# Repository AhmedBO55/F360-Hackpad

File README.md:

# F360-Hackpad
So, as a user of CAD software such as Fusion 360 and SolidWorks, most of the time I only use a small range of shortcuts, so there is basically no need for a full-size keyboard, and a macro pad is enough for the job. So, I will use 16 MX switches and a 128×32 OLED screen in order to determine the layer of the macropad. With that, I will not use a keyboard: I will use the first layer for shortcuts and the second layer for using numbers, so I will not need a keyboard.

---

# Schematics :

---

# PCB :

---

# CAD : 

---
# BOM :

1 SEED XIAO RP2040 (through-hole version)

1 0.91 inch 128*32 OLED Display

16 MX switches

16 DSA Keycaps

16 1N4148 Diodes

5 M3-16 screws

5 M3 heatset inserts

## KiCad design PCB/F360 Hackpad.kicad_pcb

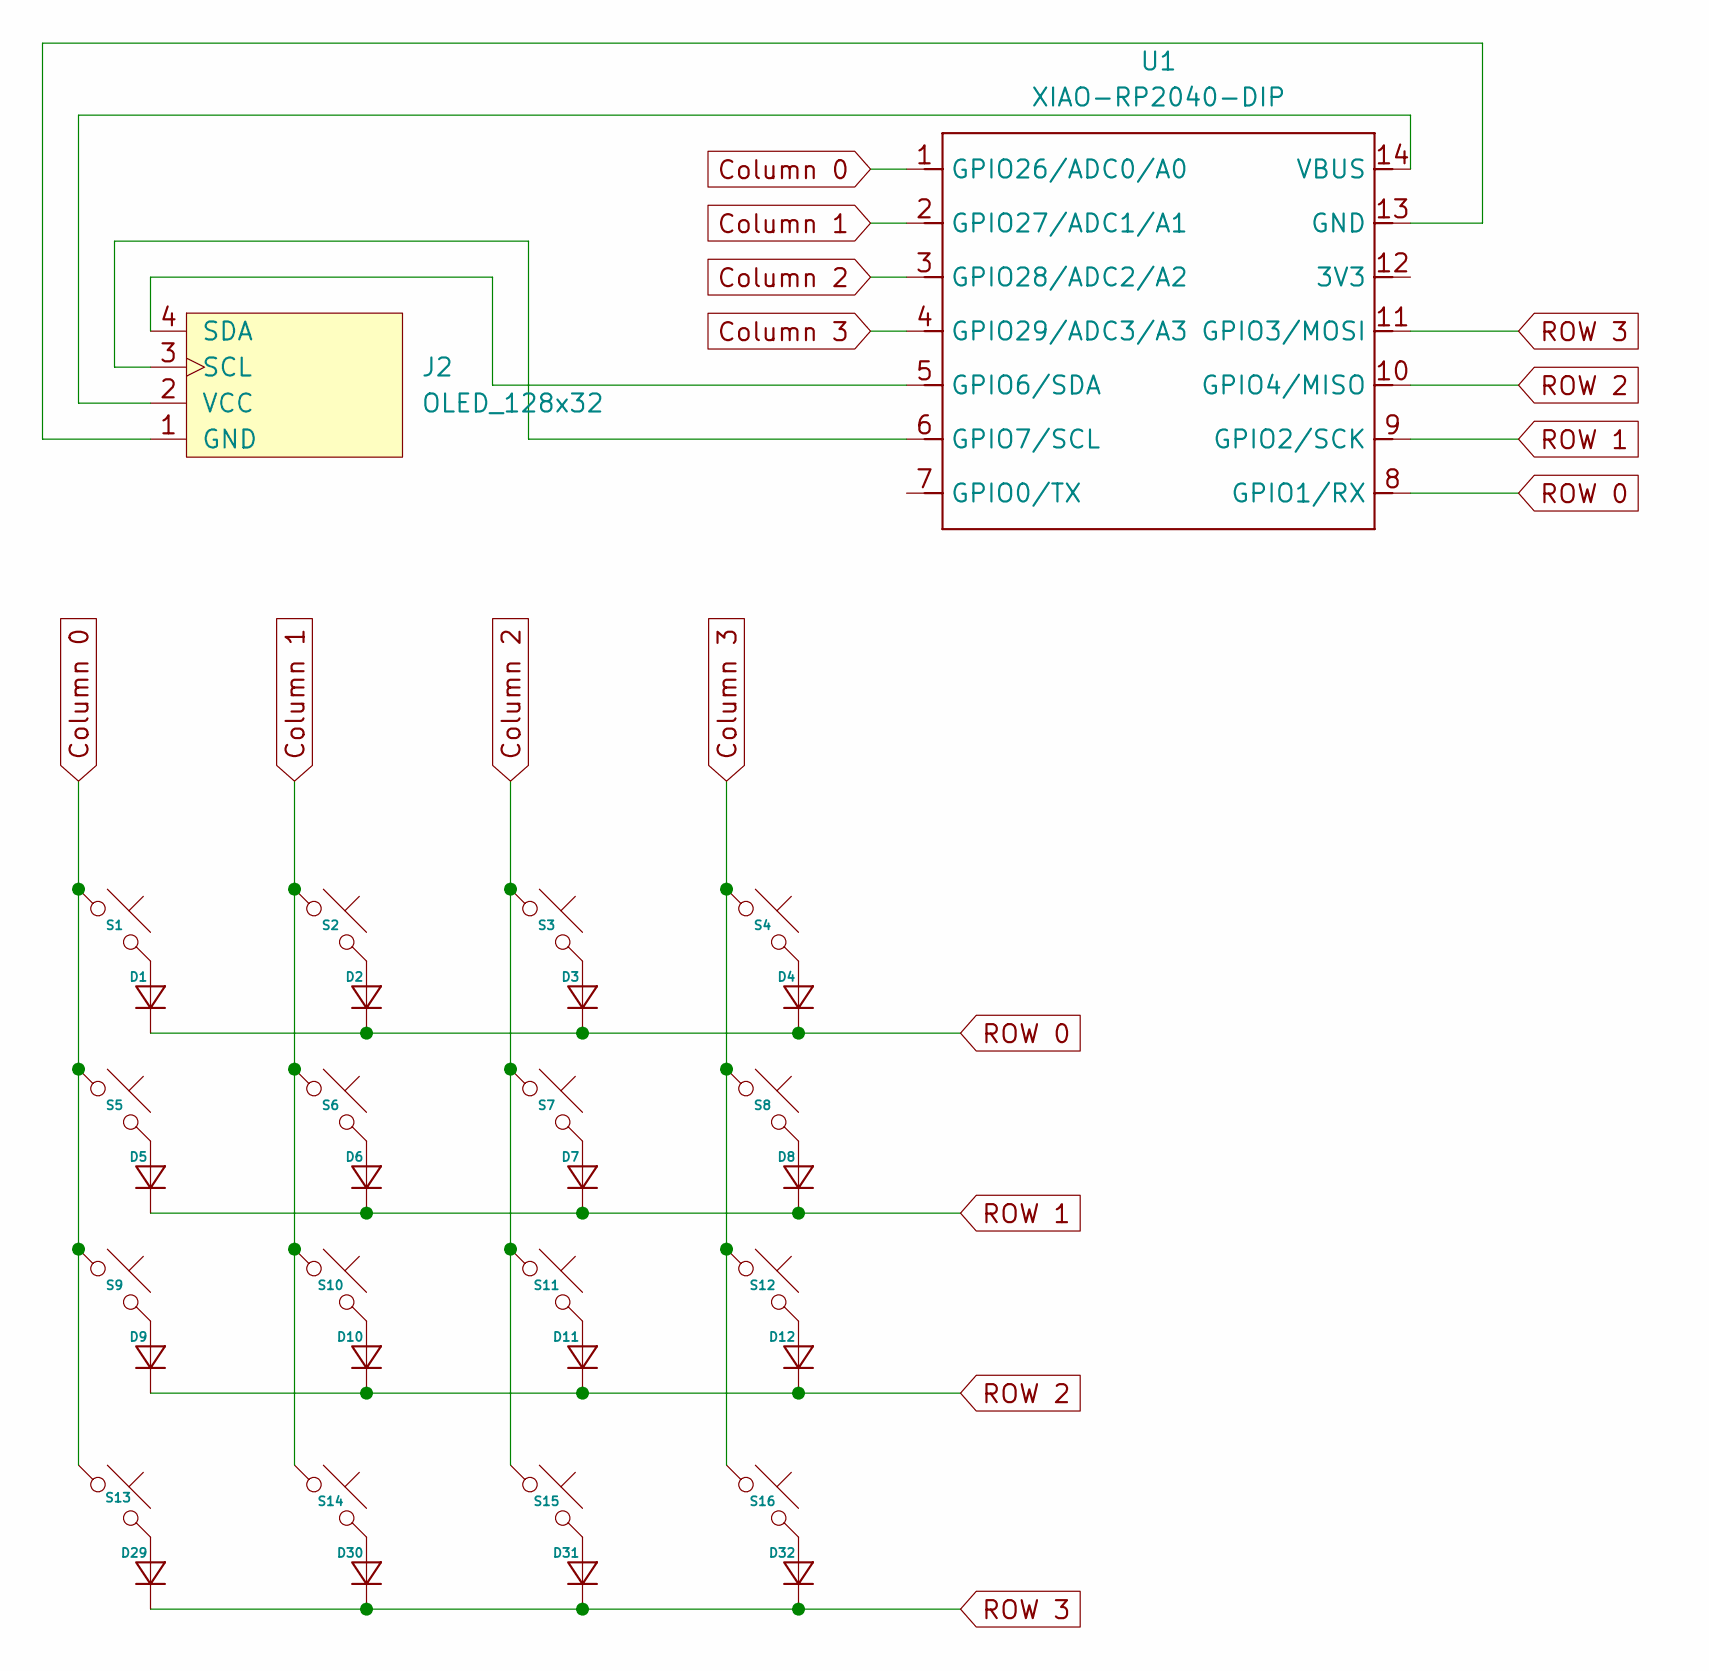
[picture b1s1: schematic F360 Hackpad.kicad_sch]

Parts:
D1, D2, D3, D4, D5, D6, D7, D8, D9, D10, D11, D12, D29, D30, D31, D32: Diode_DO-35
J2: OLED_128x32
S1, S2, S3, S4, S5, S6, S7, S8, S9, S10, S11, S12, S13, S14, S15, S16: MX_PCB_1.00u
U1: XIAO-RP2040-DIP

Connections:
Column 0: S1.1, S5.1, S9.1, S13.1, U1.1 (GPIO26/ADC0/A0)
Column 1: S2.1, S6.1, S10.1, S14.1, U1.2 (GPIO27/ADC1/A1)
Column 2: S3.1, S7.1, S11.1, S15.1, U1.3 (GPIO28/ADC2/A2)
Column 3: S4.1, S8.1, S12.1, S16.1, U1.4 (GPIO29/ADC3/A3)
unnamed: D1.2 (A), S1.2
unnamed: D2.2 (A), S2.2
unnamed: D3.2 (A), S3.2
unnamed: D4.2 (A), S4.2
unnamed: D5.2 (A), S5.2
unnamed: D6.2 (A), S6.2
unnamed: D7.2 (A), S7.2
unnamed: D8.2 (A), S8.2
unnamed: D9.2 (A), S9.2
unnamed: D10.2 (A), S10.2
unnamed: D11.2 (A), S11.2
unnamed: D12.2 (A), S12.2
unnamed: D29.2 (A), S13.2
unnamed: D30.2 (A), S14.2
unnamed: D31.2 (A), S15.2
unnamed: D32.2 (A), S16.2
unnamed: J2.1 (GND), U1.13 (GND)
unnamed: J2.3 (SCL), U1.6 (GPIO7/SCL)
unnamed: J2.4 (SDA), U1.5 (GPIO6/SDA)
unnamed: J2.2 (VCC), U1.14 (VBUS)
ROW 0: D1.1 (K), D2.1 (K), D3.1 (K), D4.1 (K), U1.8 (GPIO1/RX)
ROW 1: D5.1 (K), D6.1 (K), D7.1 (K), D8.1 (K), U1.9 (GPIO2/SCK)
ROW 2: D9.1 (K), D10.1 (K), D11.1 (K), D12.1 (K), U1.10 (GPIO4/MISO)
ROW 3: D29.1 (K), D30.1 (K), D31.1 (K), D32.1 (K), U1.11 (GPIO3/MOSI)

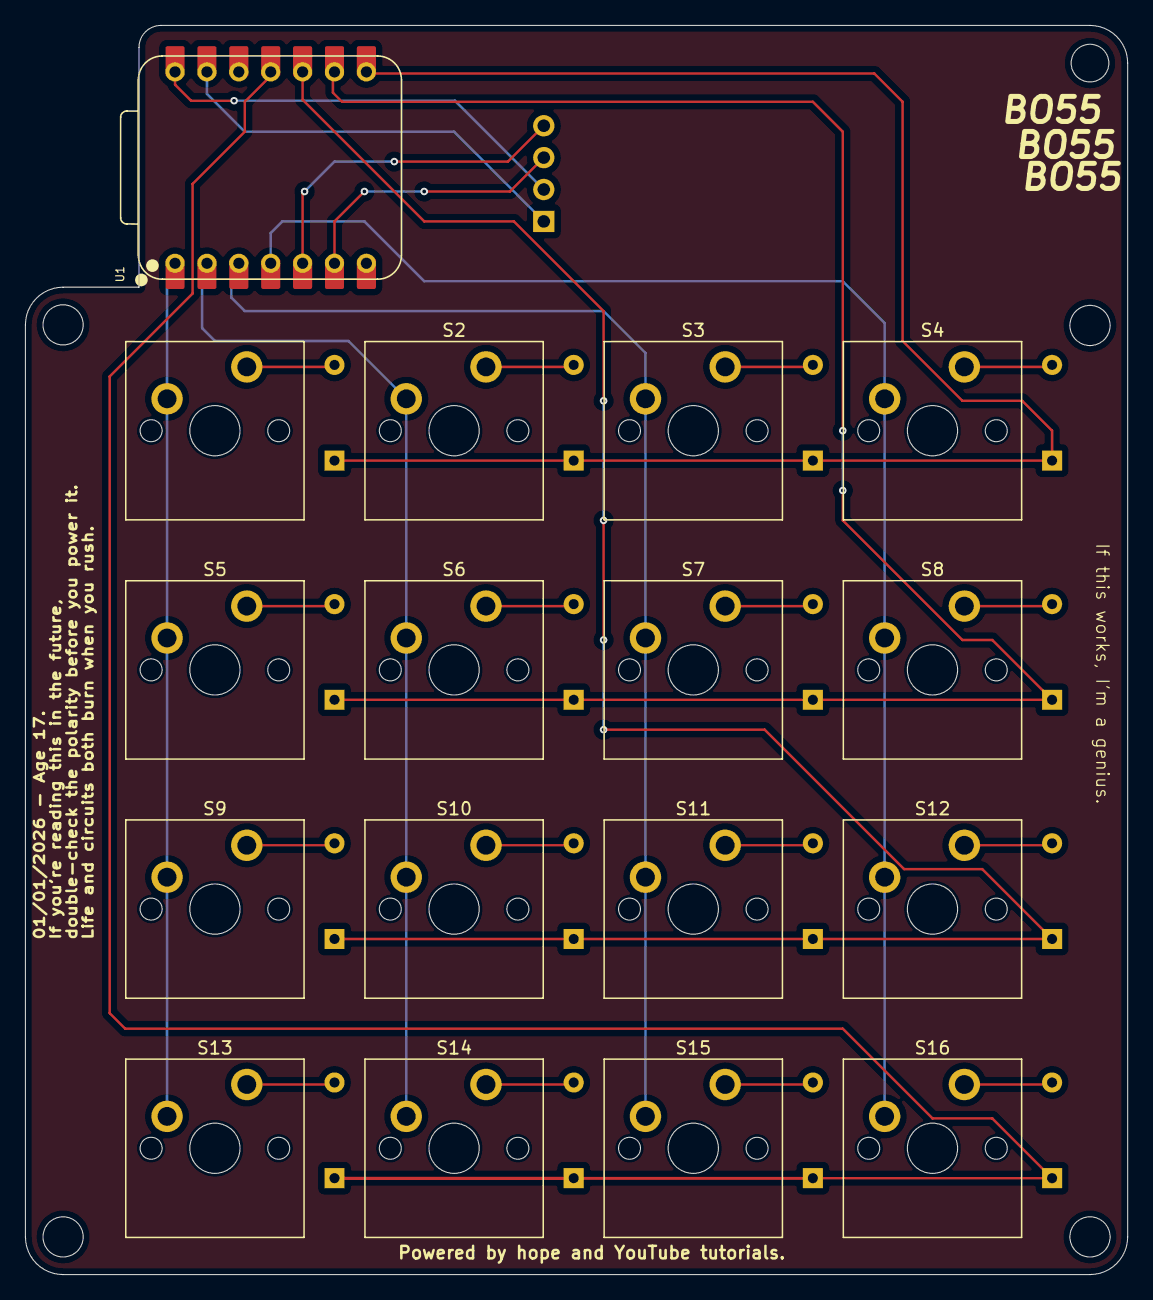
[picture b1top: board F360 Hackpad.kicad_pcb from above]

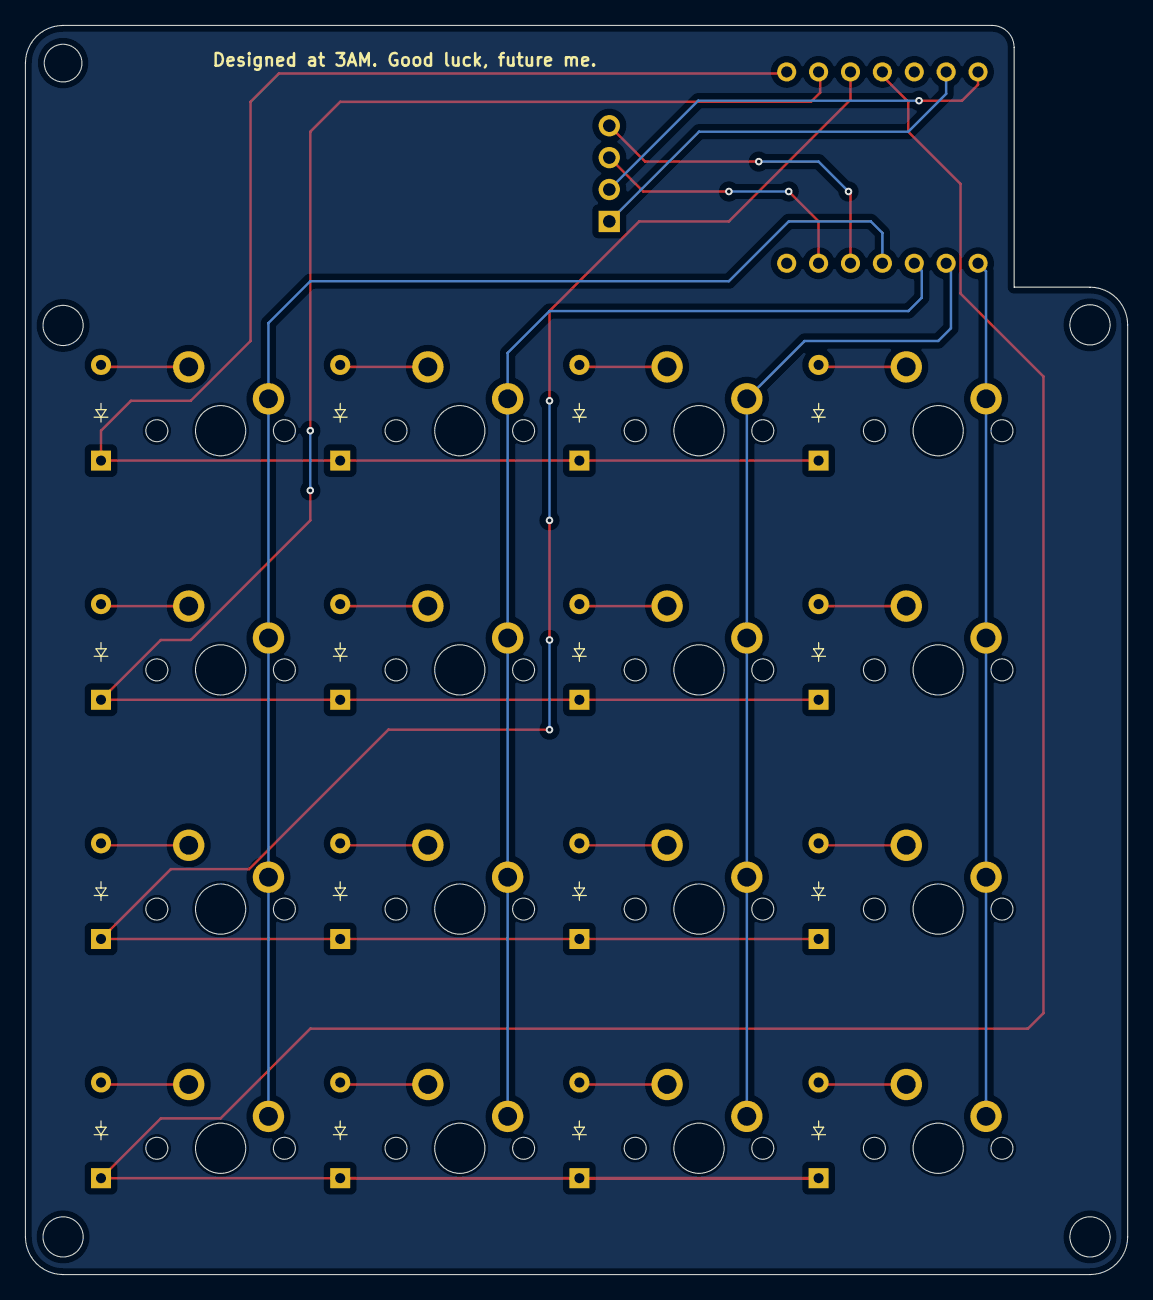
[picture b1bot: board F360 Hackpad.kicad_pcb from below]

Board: 2 copper layers, 87.8 x 99.5 mm, 34 parts (16 on the bottom side), 28 nets.

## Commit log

2026-01-02 Create h
2026-01-06 Create D
2026-01-06 Add BOM section to README
